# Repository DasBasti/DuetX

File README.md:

# DuetX
Duet electronics extension Board with up to four more stepper driver

#License
This hardware is open-source under the CERN Open Hardware License (OSH) V1.2

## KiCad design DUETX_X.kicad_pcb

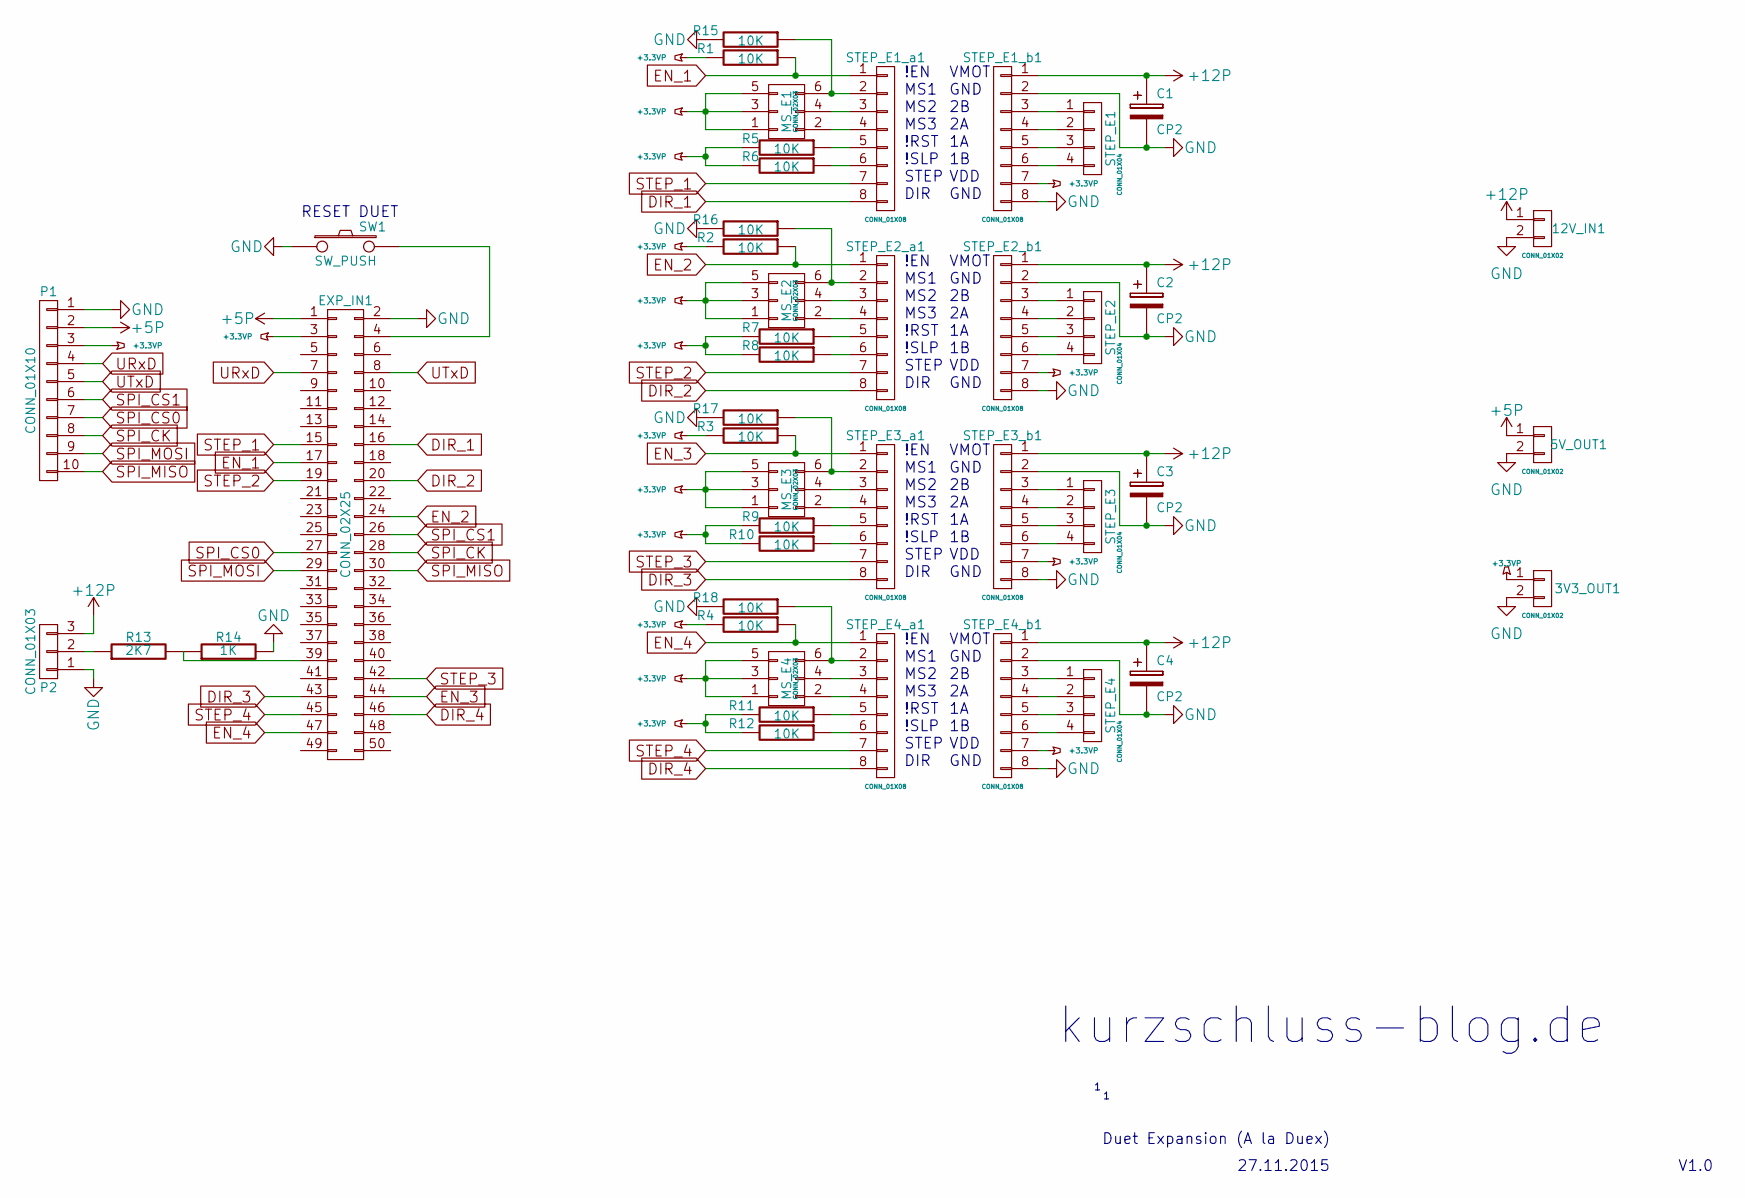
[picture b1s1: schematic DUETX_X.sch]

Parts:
3V3_OUT1, 5V_OUT1: CONN_01X02; Pin_Header_Straight_1x02
12V_IN1: CONN_01X02; mkds_1,5-2
C1, C2, C3, C4: CP2; c_elec_6.3x5.7
EXP_IN1: CONN_02X25; Pin_Header_Straight_2x25
MS_E1, MS_E2, MS_E3, MS_E4: CONN_02X03; Pin_Header_Straight_2x03
P1: CONN_01X10; Pin_Header_Straight_1x10
P2: CONN_01X03; Pin_Header_Straight_1x03
R1, R2, R3, R4, R5, R6, R7, R8, R9, R10, R11, R12, R15, R16, R17, R18: 10K; R_0603_HandSoldering
R13: 2K7; R_0603_HandSoldering
R14: 1K; R_0603_HandSoldering
STEP_E1, STEP_E2, STEP_E3, STEP_E4: CONN_01X04; Pin_Header_Straight_1x04
STEP_E1_a1, STEP_E1_b1, STEP_E2_a1, STEP_E2_b1, STEP_E3_a1, STEP_E3_b1, STEP_E4_a1, STEP_E4_b1: CONN_01X08; Pin_Header_Straight_1x08
SW1: SW_PUSH; TACT_switch

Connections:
+3.3VP: 3V3_OUT1.1, EXP_IN1.3, MS_E1.1, MS_E1.3, MS_E1.5, MS_E2.1, MS_E2.3, MS_E2.5, MS_E3.1, MS_E3.3, MS_E3.5, MS_E4.1, MS_E4.3, MS_E4.5, P1.3, R1.2, R2.2, R3.2, R4.2, R5.2, R6.2, R7.2, R8.2, R9.2, R10.2, R11.2, R12.2, STEP_E1_b1.7, STEP_E2_b1.7, STEP_E3_b1.7, STEP_E4_b1.7
+5P: 5V_OUT1.1, EXP_IN1.1, P1.2
+12P: 12V_IN1.1, C1.1, C2.1, C3.1, C4.1, P2.3, STEP_E1_b1.1, STEP_E2_b1.1, STEP_E3_b1.1, STEP_E4_b1.1
DIR_1: EXP_IN1.16, STEP_E1_a1.8
DIR_2: EXP_IN1.20, STEP_E2_a1.8
DIR_3: EXP_IN1.43, STEP_E3_a1.8
DIR_4: EXP_IN1.46, STEP_E4_a1.8
EN_1: EXP_IN1.17, R1.1, STEP_E1_a1.1
EN_2: EXP_IN1.24, R2.1, STEP_E2_a1.1
EN_3: EXP_IN1.44, R3.1, STEP_E3_a1.1
EN_4: EXP_IN1.47, R4.1, STEP_E4_a1.1
GND: 3V3_OUT1.2, 5V_OUT1.2, 12V_IN1.2, C1.2, C2.2, C3.2, C4.2, EXP_IN1.2, P1.1, P2.1, R14.2, R15.2, R16.2, R17.2, R18.2, STEP_E1_b1.2, STEP_E1_b1.8, STEP_E2_b1.2, STEP_E2_b1.8, STEP_E3_b1.2, STEP_E3_b1.8, STEP_E4_b1.2, STEP_E4_b1.8, SW1.1; also elsewhere on the board
unnamed 12: EXP_IN1.4, SW1.2; also elsewhere on the board
unnamed: EXP_IN1.39, R13.2, R14.1
unnamed: MS_E1.2, STEP_E1_a1.4
unnamed: MS_E1.4, STEP_E1_a1.3
unnamed: MS_E1.6, R15.1, STEP_E1_a1.2
unnamed: MS_E2.2, STEP_E2_a1.4
unnamed: MS_E2.4, STEP_E2_a1.3
unnamed: MS_E2.6, R16.1, STEP_E2_a1.2
unnamed: MS_E3.2, STEP_E3_a1.4
unnamed: MS_E3.4, STEP_E3_a1.3
unnamed: MS_E3.6, R17.1, STEP_E3_a1.2
unnamed: MS_E4.2, STEP_E4_a1.4
unnamed: MS_E4.4, STEP_E4_a1.3
unnamed: MS_E4.6, R18.1, STEP_E4_a1.2
unnamed: P2.2, R13.1
unnamed: R5.1, STEP_E1_a1.5
unnamed: R6.1, STEP_E1_a1.6
unnamed: R7.1, STEP_E2_a1.5
unnamed: R8.1, STEP_E2_a1.6
unnamed: R9.1, STEP_E3_a1.5
unnamed: R10.1, STEP_E3_a1.6
unnamed: R11.1, STEP_E4_a1.5
unnamed: R12.1, STEP_E4_a1.6
unnamed: STEP_E1.1, STEP_E1_b1.3
unnamed: STEP_E1.2, STEP_E1_b1.4
unnamed: STEP_E1.3, STEP_E1_b1.5
unnamed: STEP_E1.4, STEP_E1_b1.6
unnamed: STEP_E2.1, STEP_E2_b1.3
unnamed: STEP_E2.2, STEP_E2_b1.4
unnamed: STEP_E2.3, STEP_E2_b1.5
unnamed: STEP_E2.4, STEP_E2_b1.6
unnamed: STEP_E3.1, STEP_E3_b1.3
unnamed: STEP_E3.2, STEP_E3_b1.4
unnamed: STEP_E3.3, STEP_E3_b1.5
unnamed: STEP_E3.4, STEP_E3_b1.6
unnamed: STEP_E4.1, STEP_E4_b1.3
unnamed: STEP_E4.2, STEP_E4_b1.4
unnamed: STEP_E4.3, STEP_E4_b1.5
unnamed: STEP_E4.4, STEP_E4_b1.6
SPI_CK: EXP_IN1.28, P1.8
SPI_CS0: EXP_IN1.27, P1.7
SPI_CS1: EXP_IN1.26, P1.6
SPI_MISO: EXP_IN1.30, P1.10
SPI_MOSI: EXP_IN1.29, P1.9
STEP_1: EXP_IN1.15, STEP_E1_a1.7
STEP_2: EXP_IN1.19, STEP_E2_a1.7
STEP_3: EXP_IN1.42, STEP_E3_a1.7
STEP_4: EXP_IN1.45, STEP_E4_a1.7
URxD: EXP_IN1.7, P1.4
UTxD: EXP_IN1.8, P1.5

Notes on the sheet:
VMOT GND 2B 2A 1A 1B VDD GND
!EN MS1 MS2 MS3 !RST !SLP STEP DIR
RESET DUET
27.11.2015
Duet Expansion (A la Duex)
V1.0
kurzschluss-blog.de

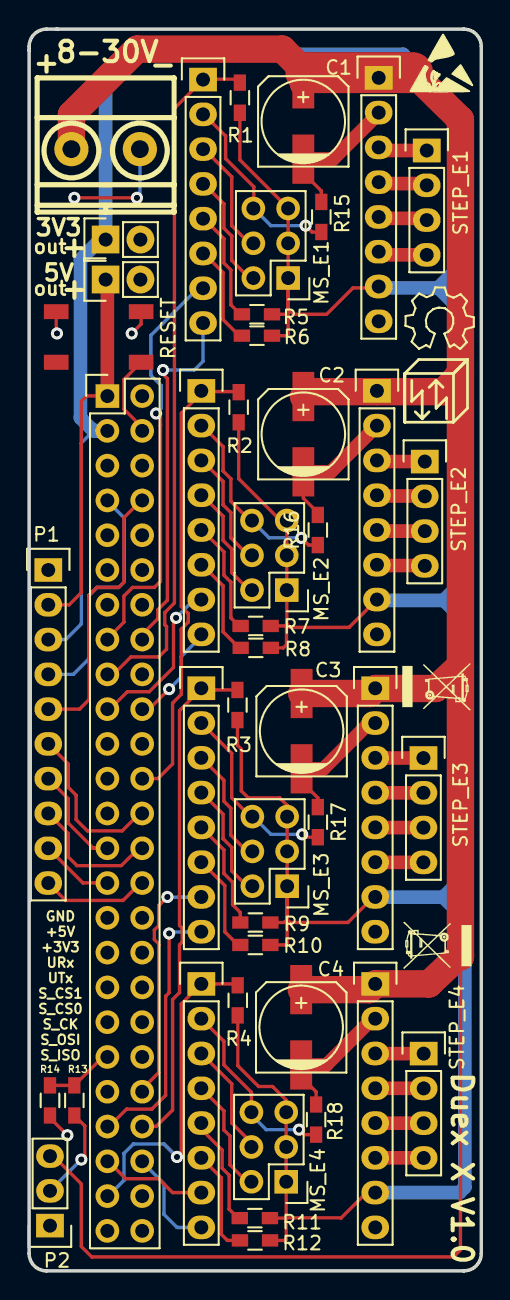
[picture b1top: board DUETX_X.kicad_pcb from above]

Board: 2 copper layers, 33.0 x 90.7 mm, 45 parts (0 on the bottom side), 62 nets.

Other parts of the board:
RESET: SW_PUSH; TACT_switch

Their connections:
GND: RESET.1; also elsewhere on the board
unnamed 12: RESET.2; also elsewhere on the board

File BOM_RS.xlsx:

ref | value | footprint | RS
EXP_IN1 | CONN_02X25 | Pin_Headers:Pin_Header_Straight_2x25 | 628-8464
STEP_E1_a1 | CONN_01X08 | Pin_Headers:Pin_Header_Straight_1x08 | 827-734
STEP_E1_b1 | CONN_01X08 | Pin_Headers:Pin_Header_Straight_1x08 | 827-734
MS_E1 | CONN_02X03 | Pin_Headers:Pin_Header_Straight_2x03 | 827-7781
STEP_E1 | CONN_01X04 | Pin_Headers:Pin_Header_Straight_1x04 | 681-2988
12V_IN1 | CONN_01X02 | sirona:mkds_1,5-2 | 425-8720
5V_OUT1 | CONN_01X02 | Pin_Headers:Pin_Header_Straight_1x02 | n_best
R5 | 10K | Resistors_SMD:R_0603_HandSoldering | 678-9667
R6 | 10K | Resistors_SMD:R_0603_HandSoldering | 678-9667
C1 | CP2 | Capacitors_SMD:c_elec_6.3x5.7 | 844-0926
STEP_E2_a1 | CONN_01X08 | Pin_Headers:Pin_Header_Straight_1x08 | 827-734
STEP_E2_b1 | CONN_01X08 | Pin_Headers:Pin_Header_Straight_1x08 | 827-734
MS_E2 | CONN_02X03 | Pin_Headers:Pin_Header_Straight_2x03 | 827-7781
STEP_E2 | CONN_01X04 | Pin_Headers:Pin_Header_Straight_1x04 | 681-2988
R7 | 10K | Resistors_SMD:R_0603_HandSoldering | 678-9667
R8 | 10K | Resistors_SMD:R_0603_HandSoldering | 678-9667
C2 | CP2 | Capacitors_SMD:c_elec_6.3x5.7 | 844-0926
STEP_E3_a1 | CONN_01X08 | Pin_Headers:Pin_Header_Straight_1x08 | 827-734
STEP_E3_b1 | CONN_01X08 | Pin_Headers:Pin_Header_Straight_1x08 | 827-734
MS_E3 | CONN_02X03 | Pin_Headers:Pin_Header_Straight_2x03 | 827-7781
STEP_E3 | CONN_01X04 | Pin_Headers:Pin_Header_Straight_1x04 | 681-2988
R9 | 10K | Resistors_SMD:R_0603_HandSoldering | 678-9667
R10 | 10K | Resistors_SMD:R_0603_HandSoldering | 678-9667
C3 | CP2 | Capacitors_SMD:c_elec_6.3x5.7 | 844-0926
STEP_E4_a1 | CONN_01X08 | Pin_Headers:Pin_Header_Straight_1x08 | 827-734
STEP_E4_b1 | CONN_01X08 | Pin_Headers:Pin_Header_Straight_1x08 | 827-734
MS_E4 | CONN_02X03 | Pin_Headers:Pin_Header_Straight_2x03 | 827-7781
STEP_E4 | CONN_01X04 | Pin_Headers:Pin_Header_Straight_1x04 | 681-2988
R11 | 10K | Resistors_SMD:R_0603_HandSoldering | 678-9667
R12 | 10K | Resistors_SMD:R_0603_HandSoldering | 678-9667
C4 | CP2 | Capacitors_SMD:c_elec_6.3x5.7 | 844-0926
3V3_OUT1 | CONN_01X02 | Pin_Headers:Pin_Header_Straight_1x02 | n_best
R4 | 10K | Resistors_SMD:R_0603_HandSoldering | 678-9667
R3 | 10K | Resistors_SMD:R_0603_HandSoldering | 678-9667
R2 | 10K | Resistors_SMD:R_0603_HandSoldering | 678-9667
R1 | 10K | Resistors_SMD:R_0603_HandSoldering | 678-9667
SW1 | SW_PUSH | sirona:TACT_switch
P1 | CONN_01X10 | Pin_Headers:Pin_Header_Straight_1x10 | n_best
P2 | CONN_01X03 | Pin_Headers:Pin_Header_Straight_1x03 | n_best
R13 | 2K7 | Resistors_SMD:R_0603_HandSoldering | n_best
R14 | 1K | Resistors_SMD:R_0603_HandSoldering | n_best
R18 | 10K | Resistors_SMD:R_0603_HandSoldering | 678-9667
R17 | 10K | Resistors_SMD:R_0603_HandSoldering | 678-9667
R16 | 10K | Resistors_SMD:R_0603_HandSoldering | 678-9667
R15 | 10K | Resistors_SMD:R_0603_HandSoldering | 678-9667
 |  |  | 462.3
 |  |  | 15.41
 |  | Driver 4 Stk 5€
 |  | PCB 42€

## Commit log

2016-03-07 Added files via upload
    inital commit of schematic, BOM, 3D rendering and building instructions
2016-03-08 Gerber Files for PCB manufacturing
2016-03-08 Schematics and KiCad project
